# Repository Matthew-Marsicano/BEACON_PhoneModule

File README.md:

# BEACON Phone Module

KiCad 10 project for the BEACON phone module: a MagSafe-mounted board with an nRF52840, a 2.4 GHz receive chain
(patch antenna → BPF → LNA → nRF) and a CW transmit chain (LMX2582 synthesizer → CC2595 PA → U.FL to a Taoglas
FXP70 flex antenna). It is powered over USB-C.

**Ordering boards:** follow [`fab/JLCPCB_ORDER.md`](fab/JLCPCB_ORDER.md) (files to upload, board options, parts to check).
The wearable tag's JLCPCB package (exported from its Altium project) is in [`fab/wearable/`](fab/wearable/JLCPCB_ORDER.md).
To order both boards together, [`fab/panel/`](fab/panel/PANEL_ORDER.md) has a combined panel (one of each) with a merged BOM and CPL.

## Opening the project

Open `BEACON_PhoneModule.kicad_pro` in KiCad 10. The project's own libraries are referenced relative to the project
folder (`BEACON.kicad_sym`, `BEACON.pretty`, `BEACON_Routed.pretty`), so no library setup is needed.

| Path | Contents |
|---|---|
| `*.kicad_sch` | Root schematic + 6 sheets: USB, Power, MCU, RX_Frontend, TX_PA, CW_Synth |
| `BEACON_PhoneModule.kicad_pcb` | 4-layer board, 55 × 78.45 mm |
| `BEACON_PhoneModule.kicad_dru` | Custom design rules (JLCPCB limits, RF CPWG, USB pair, nRF aQFN escape) |
| `docs/` | Design notes, stackup and impedance, BOM (LCSC), reviews, hand-routing notes |
| `scripts/` | Python scripts used to generate and post-process the board (run with KiCad's Python) |
| `enclosure/` | OpenSCAD enclosure variants, STL and renders |
| `fab/` | JLCPCB outputs: Gerber/drill zip, BOM, CPL, PDFs, STEP, the one-zip package and the order sheet |
| `fab/wearable/` | Wearable tag JLCPCB outputs (Altium export): Gerber/drill zip, BOM, CPL, OutJob, order sheet |

## Board rules worth knowing

- **Stackup:** JLC04161H-7628, 1.6 mm. L1 signals and RF, **L2 solid GND (no tracks)**, L3 3V3 / VCC_SYN planes,
  L4 signals and USB pair.
- **No GND traces.** GND is copper fills on every layer plus vias; each GND pad has its own via to L2.
  3V3 and VCC_SYN pads have vias to their L3 areas. 5V0 and 5V_BUS are fills.
- **RF:** 50 Ω CPWG, 0.335 mm track, 0.203 mm gap, L1 only. RF and the USB D+/D− pair are locked; don't move them.
- **Vias:** 0.45/0.25 mm everywhere; 0.30/0.15 mm only as via-in-pad on the nRF (U5) balls. Order with
  JLC via-in-pad (POFV, filled and capped), ENIG and impedance control.
- Run DRC (Inspect → Design Rules Checker) before every commit. The remaining work is tracked in GitHub Issues.

## Working together

- **One person edits the PCB at a time.** `.kicad_pcb` is text, but two people's board edits don't merge cleanly.
  Say in the issue or team chat when you take the board, and push when you hand it back.
- Schematic sheets can be edited in parallel by different people (one sheet each).
- Save in KiCad, close the editor, then commit. Keep commits small and say what changed.

## Finishing steps (after routing is complete)

Run from this folder with KiCad's Python (`D:/KiCAD/bin/python.exe -I` on the original machine; adjust the path):

1. `scripts/stitch.py`: GND via fences along RF lines, perimeter and 3 mm grid stitching.
2. `kicad-cli pcb drc --format json -o drc.json BEACON_PhoneModule.kicad_pcb`, then `scripts/bridge_fills.py drc.json`
   to join any fill islands that are left unconnected.
3. `scripts/finish.py`: silkscreen clean-up and zone refill.
4. Final DRC with `--schematic-parity --refill-zones`, then `scripts/export_fab.py` (Gerbers, drill, BOM, CPL, STEP).

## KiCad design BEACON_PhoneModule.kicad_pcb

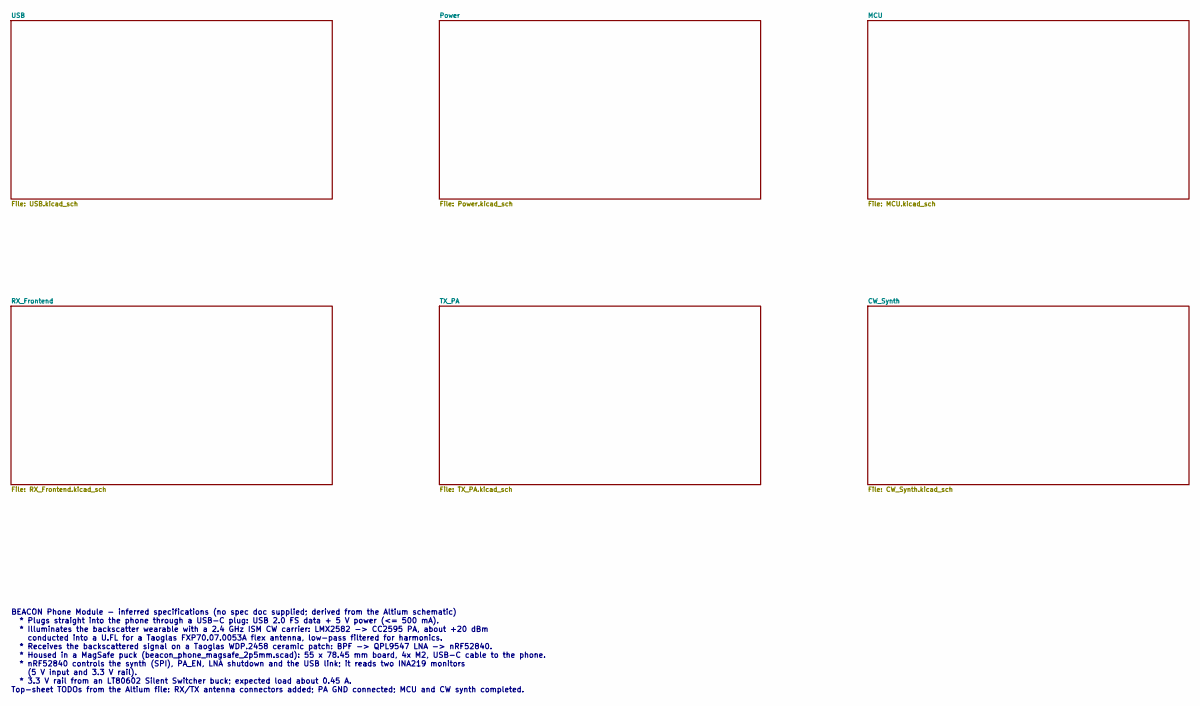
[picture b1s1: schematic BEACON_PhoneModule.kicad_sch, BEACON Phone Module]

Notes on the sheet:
BEACON Phone Module - inferred specifications (no spec doc supplied; derived from the Altium schematic) * Plugs straight into the phone through a USB-C plug: USB 2.0 FS data + 5 V power (<= 500 mA). * Illuminates the backscatter wearable with a 2.4 GHz ISM CW carrier: LMX2582 -> CC2595 PA, about +2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

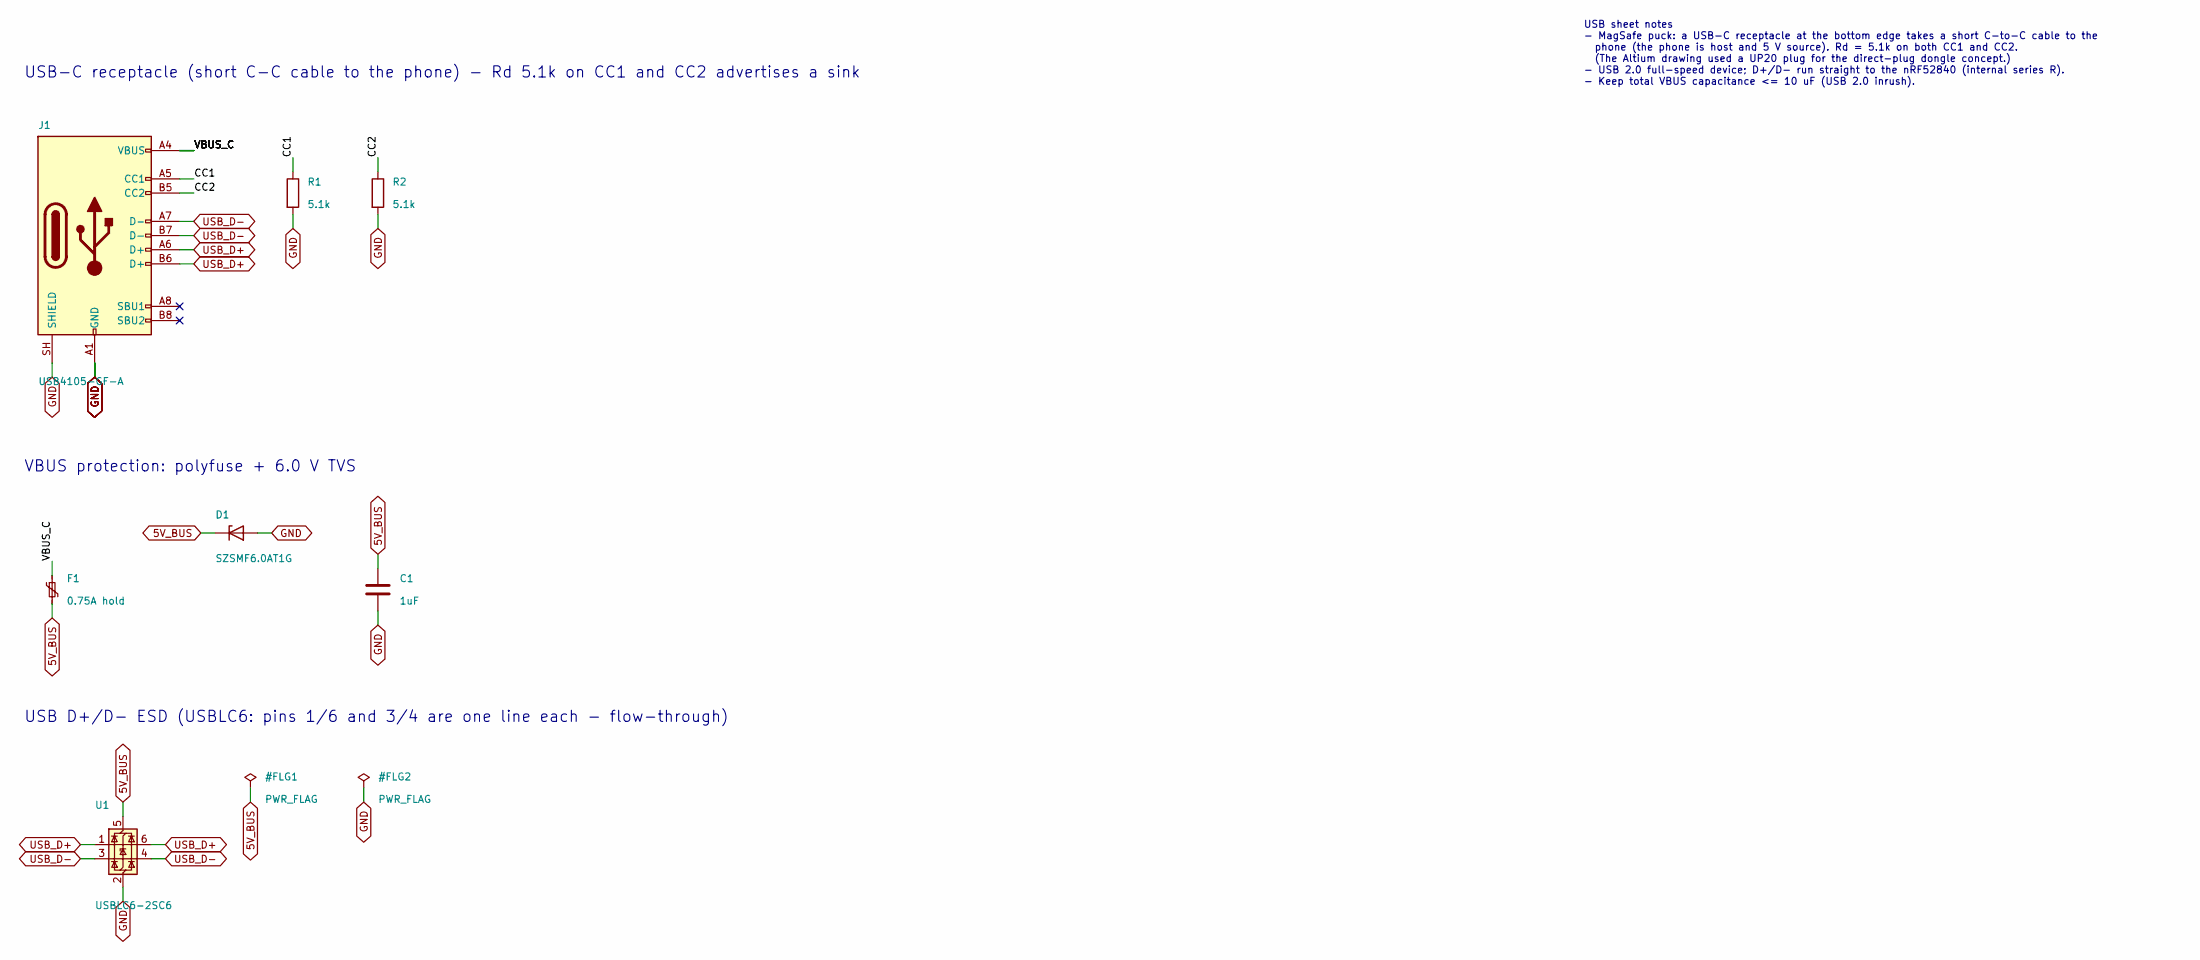
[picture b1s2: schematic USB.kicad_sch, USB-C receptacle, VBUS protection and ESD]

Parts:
C1: 1uF; C1_C_0402_1005Metric
D1: SZSMF6.0AT1G; D1_D_SOD-123F; MPN SZSMF6.0AT1G
F1: 0.75A hold; F1_Fuse_1206_3216Metric; MPN NANOSMDC075F-2
J1: USB4105-GF-A; J1_USB_C_Receptacle_GCT_USB4105-xx-A_16P_TopMnt_Horizontal; MPN USB4105-GF-A
R1: 5.1k; R1_R_0402_1005Metric
R2: 5.1k; R2_R_0402_1005Metric
U1: USBLC6-2SC6; U1_SOT-23-6; MPN USBLC6-2SC6

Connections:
5V_BUS: C1.1, D1.1 (K), F1.2, U1.5 (VBUS); also elsewhere on the board
/USB/CC1: J1.A5 (CC1), R1.1
/USB/CC2: J1.B5 (CC2), R2.1
/USB/VBUS_C: F1.1, J1.A4 (VBUS), J1.A9 (VBUS), J1.B4 (VBUS), J1.B9 (VBUS)
GND: C1.2, D1.2 (A), J1.A1 (GND), J1.A12 (GND), J1.B1 (GND), J1.B12 (GND), J1.SH (SHIELD), R1.2, R2.2, U1.2 (GND); also elsewhere on the board
USB_D+: J1.A6 (D+), J1.B6 (D+), U1.1 (I/O1), U1.6 (I/O1); also elsewhere on the board
USB_D-: J1.A7 (D-), J1.B7 (D-), U1.3 (I/O2), U1.4 (I/O2); also elsewhere on the board

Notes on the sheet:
USB-C receptacle (short C-C cable to the phone) - Rd 5.1k on CC1 and CC2 advertises a sink
VBUS protection: polyfuse + 6.0 V TVS
USB D+/D- ESD (USBLC6: pins 1/6 and 3/4 are one line each - flow-through)
USB sheet notes - MagSafe puck: a USB-C receptacle at the bottom edge takes a short C-to-C cable to the phone (the phone is host and 5 V source). Rd = 5.1k on both CC1 and CC2. (The Altium drawing used a UP20 plug for the direct-plug dongle concept.) - USB 2.0 full-speed device; D+/D- run straight 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

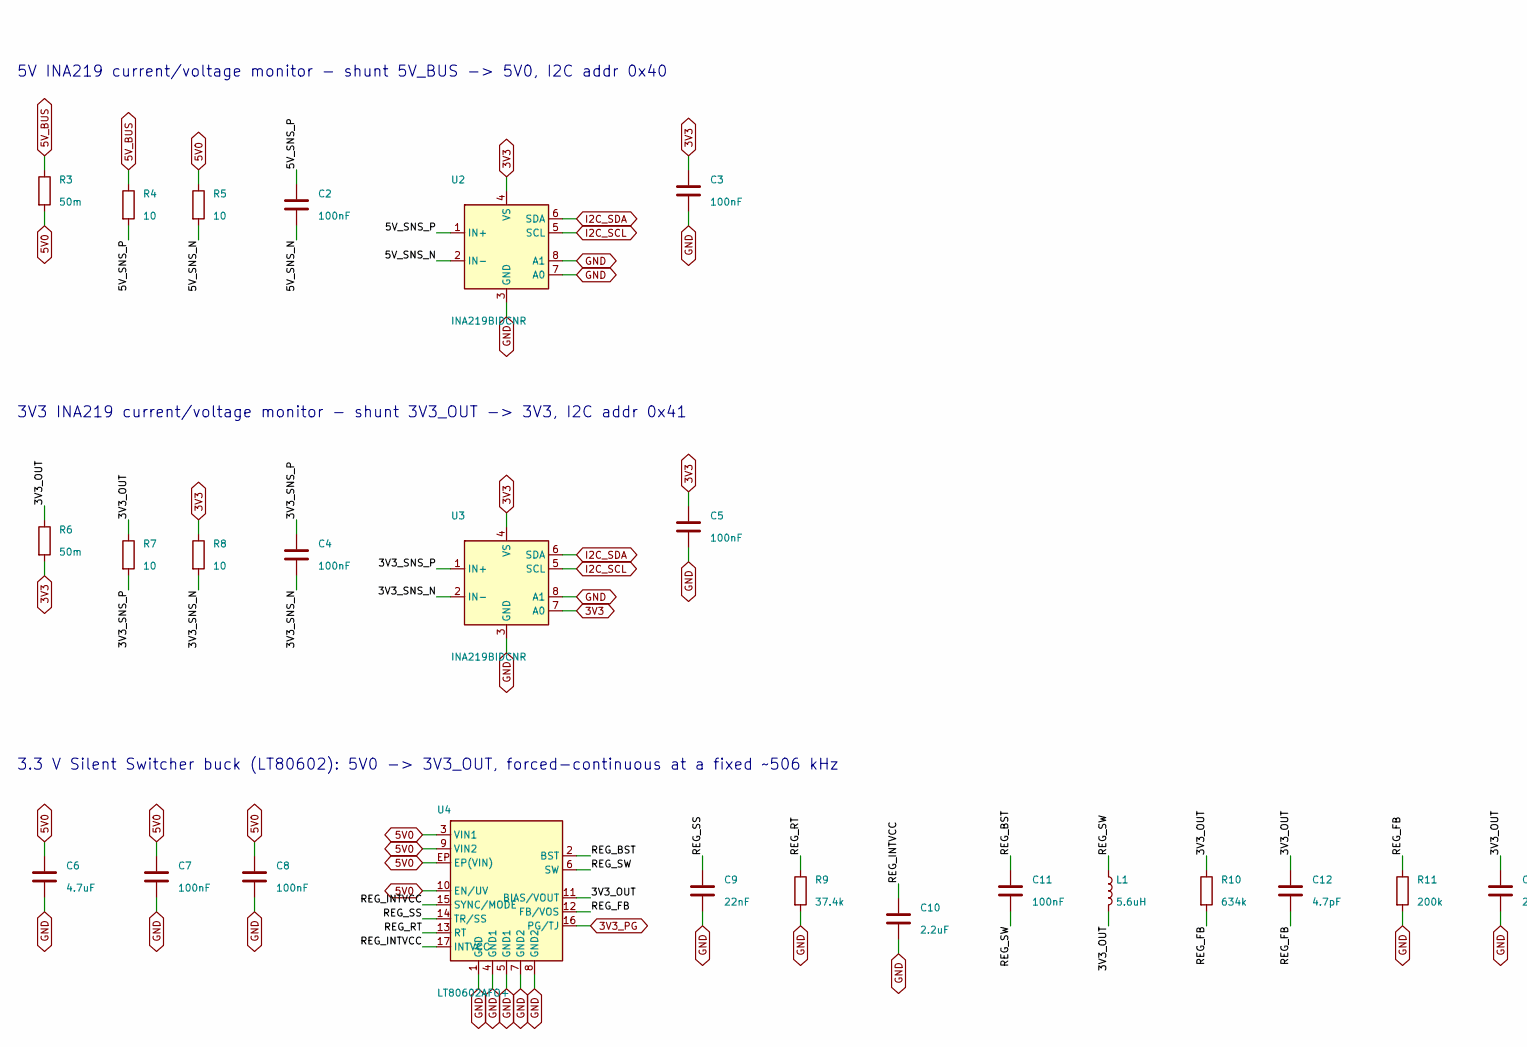
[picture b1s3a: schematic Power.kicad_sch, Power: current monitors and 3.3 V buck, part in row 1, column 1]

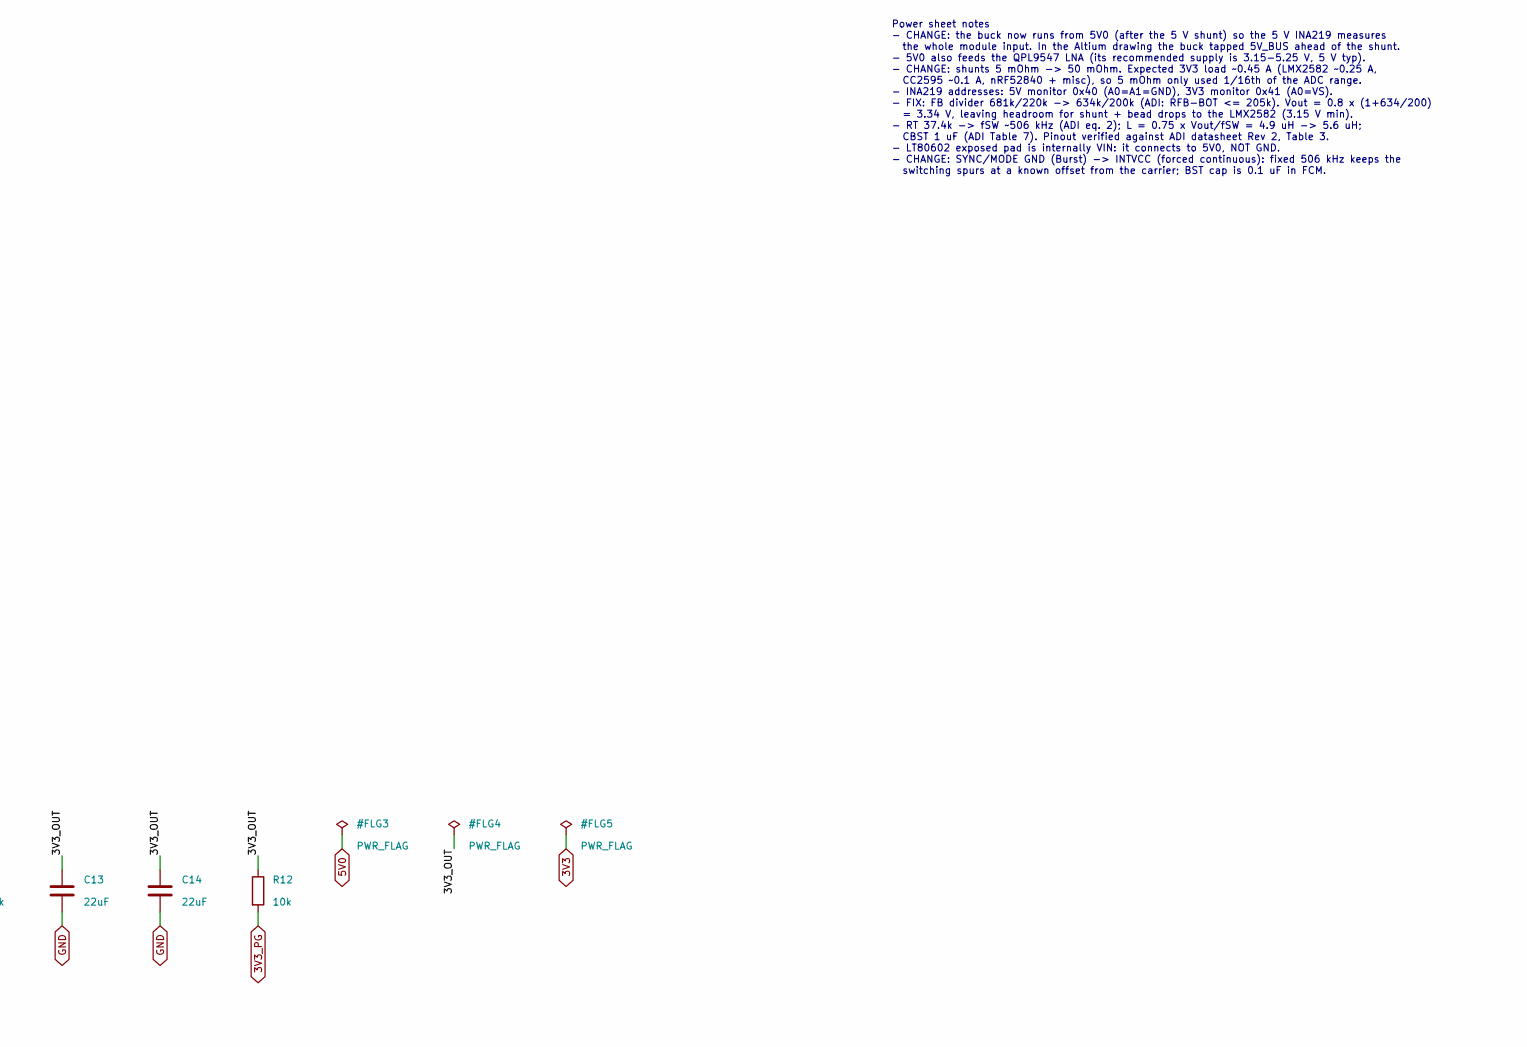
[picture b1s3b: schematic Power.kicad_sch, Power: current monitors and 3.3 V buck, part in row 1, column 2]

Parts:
C2: 100nF; C2_C_0402_1005Metric
C3: 100nF; C3_C_0402_1005Metric
C4: 100nF; C4_C_0402_1005Metric
C5: 100nF; C5_C_0402_1005Metric
C6: 4.7uF; C6_C_0603_1608Metric
C7: 100nF; C7_C_0402_1005Metric
C8: 100nF; C8_C_0402_1005Metric
C9: 22nF; C9_C_0402_1005Metric
C10: 2.2uF; C10_C_0603_1608Metric
C11: 100nF; C11_C_0402_1005Metric
C12: 4.7pF; C12_C_0402_1005Metric
C13: 22uF; C13_C_0805_2012Metric
C14: 22uF; C14_C_0805_2012Metric
L1: 5.6uH; L1_L_Abracon_ASPI-4030S; MPN ASPI-4030S-5R6M-T; LCSC C5224561
R3: 50m; R3_R_0805_2012Metric; Tolerance 1%; MPN ERJ-6BWFR050V
R4: 10; R4_R_0402_1005Metric
R5: 10; R5_R_0402_1005Metric
R6: 50m; R6_R_0805_2012Metric; Tolerance 1%; MPN ERJ-6BWFR050V
R7: 10; R7_R_0402_1005Metric
R8: 10; R8_R_0402_1005Metric
R9: 37.4k; R9_R_0402_1005Metric
R10: 634k; R10_R_0402_1005Metric
R11: 200k; R11_R_0402_1005Metric
R12: 10k; R12_R_0402_1005Metric
U2: INA219BIDCNR; U2_SOT-23-8; MPN INA219BIDCNR
U3: INA219BIDCNR; U3_SOT-23-8; MPN INA219BIDCNR
U4: LT80602AFO+; U4_ADI_FC2QFN-17-1EP_3x3mm_LT80602; MPN LT80602AFO+; LCSC C54448890

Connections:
3V3: C3.1, C5.1, R6.2, R8.1, U2.4 (VS), U3.4 (VS), U3.7 (A0); also elsewhere on the board
3V3_PG: R12.2, U4.16 (PG/TJ); also elsewhere on the board
5V0: C6.1, C7.1, C8.1, R3.2, R5.1, U4.3 (VIN1), U4.9 (VIN2), U4.10 (EN/UV), U4.EP (EP(VIN)); also elsewhere on the board
5V_BUS: R3.1, R4.1; also elsewhere on the board
/Power/3V3_OUT: C12.1, C13.1, C14.1, L1.2, R6.1, R7.1, R10.1, R12.1, U4.11 (BIAS/VOUT)
/Power/3V3_SNS_N: C4.2, R8.2, U3.2 (IN-)
/Power/3V3_SNS_P: C4.1, R7.2, U3.1 (IN+)
/Power/5V_SNS_N: C2.2, R5.2, U2.2 (IN-)
/Power/5V_SNS_P: C2.1, R4.2, U2.1 (IN+)
/Power/REG_BST: C11.1, U4.2 (BST)
/Power/REG_FB: C12.2, R10.2, R11.1, U4.12 (FB/VOS)
/Power/REG_INTVCC: C10.1, U4.15 (SYNC/MODE), U4.17 (INTVCC)
/Power/REG_RT: R9.1, U4.13 (RT)
/Power/REG_SS: C9.1, U4.14 (TR/SS)
/Power/REG_SW: C11.2, L1.1, U4.6 (SW)
GND: C3.2, C5.2, C6.2, C7.2, C8.2, C9.2, C10.2, C13.2, C14.2, R9.2, R11.2, U2.3 (GND), U2.7 (A0), U2.8 (A1), U3.3 (GND), U3.8 (A1), U4.1 (GND), U4.4 (GND1), U4.5 (GND1), U4.7 (GND2), U4.8 (GND2); also elsewhere on the board
I2C_SCL: U2.5 (SCL), U3.5 (SCL); also elsewhere on the board
I2C_SDA: U2.6 (SDA), U3.6 (SDA); also elsewhere on the board

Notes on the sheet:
5V INA219 current/voltage monitor - shunt 5V_BUS -> 5V0, I2C addr 0x40
3V3 INA219 current/voltage monitor - shunt 3V3_OUT -> 3V3, I2C addr 0x41
3.3 V Silent Switcher buck (LT80602): 5V0 -> 3V3_OUT, forced-continuous at a fixed ~506 kHz
Power sheet notes - CHANGE: the buck now runs from 5V0 (after the 5 V shunt) so the 5 V INA219 measures the whole module input. In the Altium drawing the buck tapped 5V_BUS ahead of the shunt. - 5V0 also feeds the QPL9547 LNA (its recommended supply is 3.15-5.25 V, 5 V typ). - CHANGE: shunts 5 mOhm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

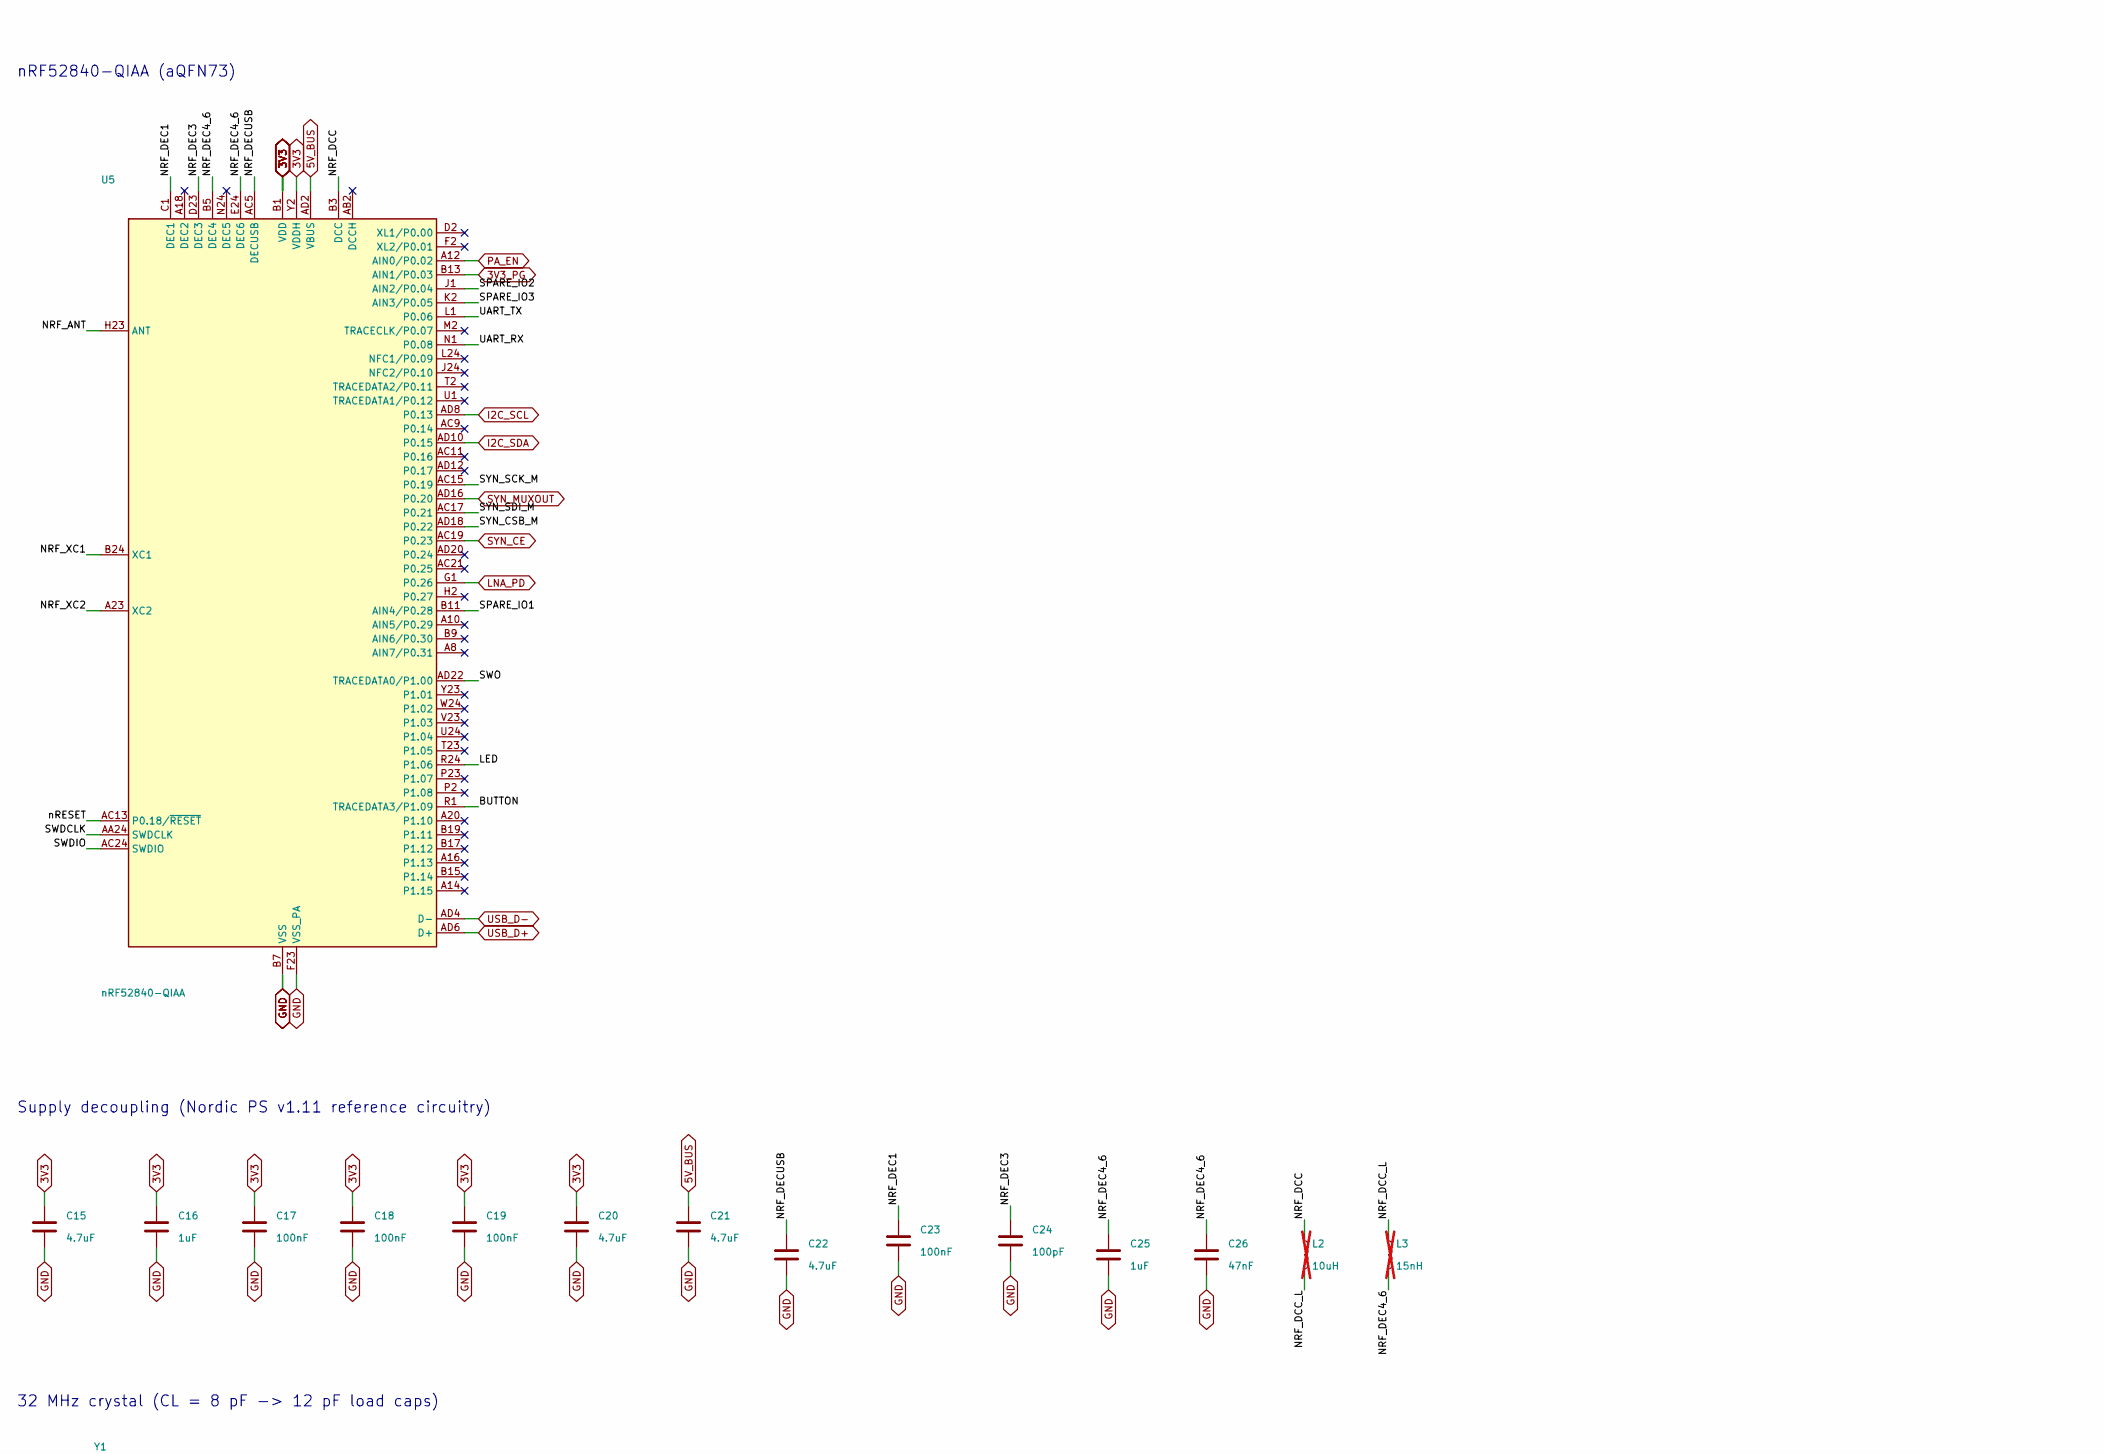
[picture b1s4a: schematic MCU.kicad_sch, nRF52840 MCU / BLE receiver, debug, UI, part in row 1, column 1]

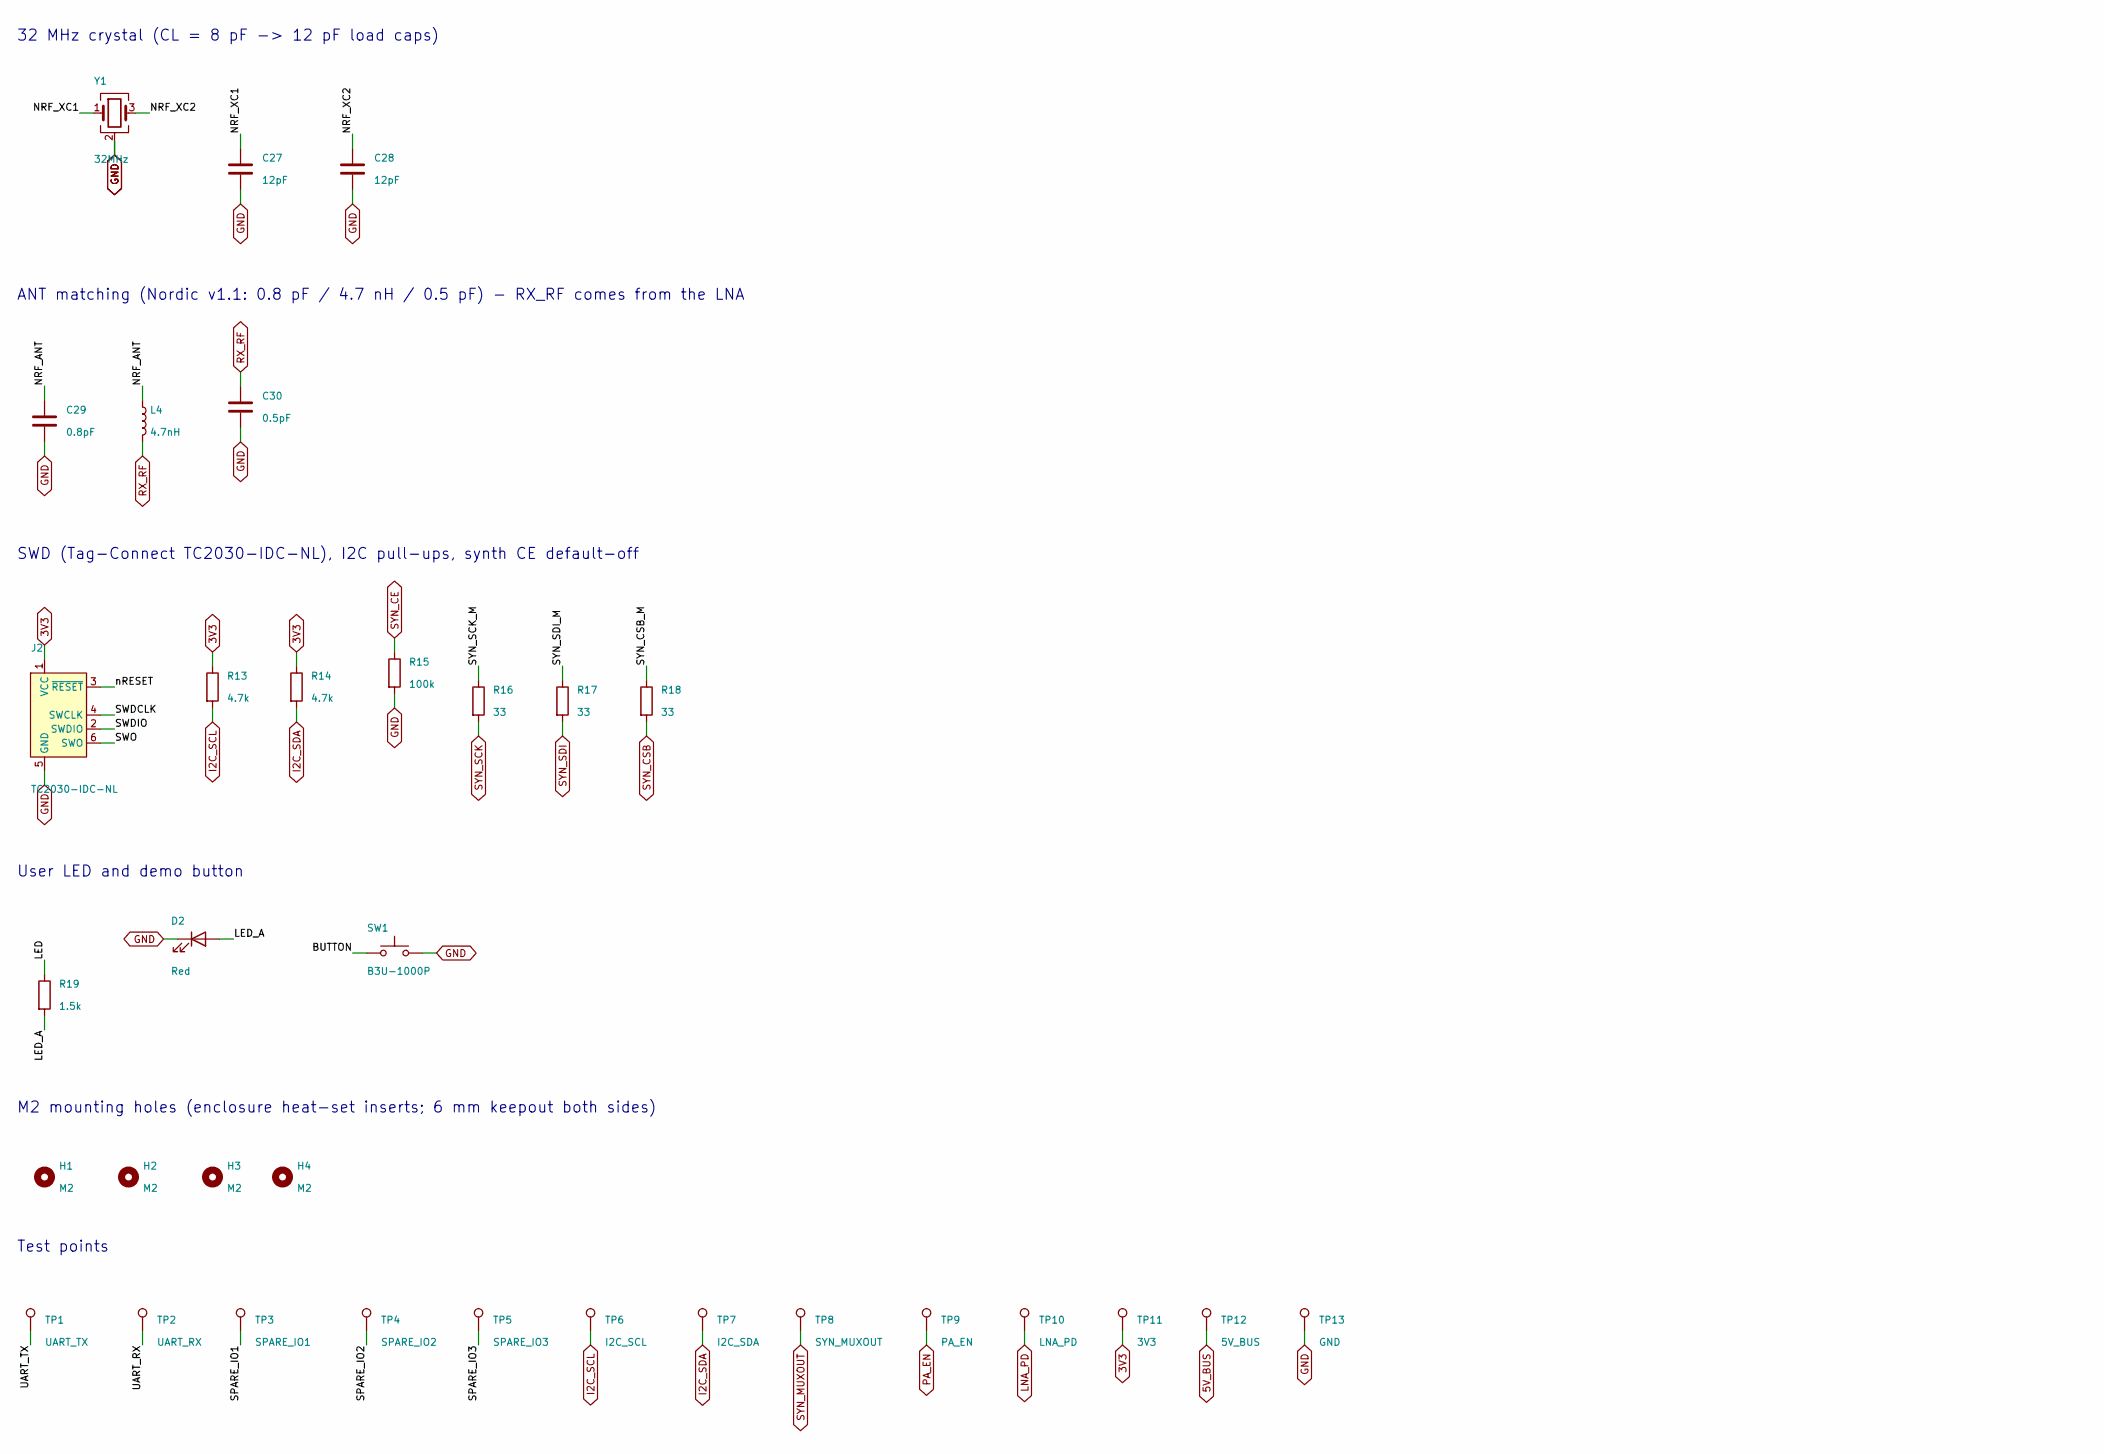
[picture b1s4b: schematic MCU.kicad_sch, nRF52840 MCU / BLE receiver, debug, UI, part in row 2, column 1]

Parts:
C15: 4.7uF; C15_C_0603_1608Metric
C16: 1uF; C16_C_0402_1005Metric
C17: 100nF; C17_C_0402_1005Metric
C18: 100nF; C18_C_0402_1005Metric
C19: 100nF; C19_C_0402_1005Metric
C20: 4.7uF; C20_C_0603_1608Metric
C21: 4.7uF; C21_C_0603_1608Metric
C22: 4.7uF; C22_C_0603_1608Metric
C23: 100nF; C23_C_0402_1005Metric
C24: 100pF; C24_C_0402_1005Metric
C25: 1uF; C25_C_0402_1005Metric
C26: 47nF; C26_C_0402_1005Metric
C27: 12pF; C27_C_0402_1005Metric
C28: 12pF; C28_C_0402_1005Metric
C29: 0.8pF; C29_C_0402_1005Metric; MPN GJM1555C1HR80BB01D
C30: 0.5pF; C30_C_0402_1005Metric; MPN GJM1555C1HR50BB01D
D2: Red; D2_LED_0603_1608Metric; MPN KT-0603R
H1: M2; H1_MountingHole_2.2mm_M2
H2: M2; H2_MountingHole_2.2mm_M2
H3: M2; H3_MountingHole_2.2mm_M2
H4: M2; H4_MountingHole_2.2mm_M2
J2: TC2030-IDC-NL; J2_Tag-Connect_TC2030-IDC-NL_2x03_P1.27mm_Vertical
L2: 10uH; L2_L_0603_1608Metric; MPN LQM18PN100MFRL; not fitted
L3: 15nH; L3_L_0402_1005Metric; MPN LQG15HS15NJ02D; not fitted
L4: 4.7nH; L4_L_0402_1005Metric; MPN LQG15HS4N7B02D; LCSC C162543
R13: 4.7k; R13_R_0402_1005Metric
R14: 4.7k; R14_R_0402_1005Metric
R15: 100k; R15_R_0402_1005Metric
R16: 33; R16_R_0402_1005Metric
R17: 33; R17_R_0402_1005Metric
R18: 33; R18_R_0402_1005Metric
R19: 1.5k; R19_R_0402_1005Metric
SW1: B3U-1000P; SW1_SW_SPST_B3U-1000P; MPN B3U-1000P
TP1: UART_TX; TP1_TestPoint_Pad_D1.0mm
TP2: UART_RX; TP2_TestPoint_Pad_D1.0mm
TP3: SPARE_IO1; TP3_TestPoint_Pad_D1.0mm
TP4: SPARE_IO2; TP4_TestPoint_Pad_D1.0mm
TP5: SPARE_IO3; TP5_TestPoint_Pad_D1.0mm
TP6: I2C_SCL; TP6_TestPoint_Pad_D1.0mm
TP7: I2C_SDA; TP7_TestPoint_Pad_D1.0mm
TP8: SYN_MUXOUT; TP8_TestPoint_Pad_D1.0mm
TP9: PA_EN; TP9_TestPoint_Pad_D1.0mm
TP10: LNA_PD; TP10_TestPoint_Pad_D1.0mm
TP11: 3V3; TP11_TestPoint_Pad_D1.0mm
TP12: 5V_BUS; TP12_TestPoint_Pad_D1.0mm
TP13: GND; TP13_TestPoint_Pad_D1.0mm
U5: nRF52840-QIAA; U5_Nordic_AQFN-73-1EP_7x7mm_P0.5mm; MPN NRF52840-QIAA-R
Y1: 32MHz; Y1_Crystal_SMD_2016-4Pin_2.0x1.6mm; MPN ABM11W-32.0000MHZ-8-B1U-T3

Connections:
3V3: C15.1, C16.1, C17.1, C18.1, C19.1, C20.1, J2.1 (VCC), R13.1, R14.1, TP11.1, U5.A22 (VDD), U5.AD14 (VDD), U5.AD23 (VDD), U5.B1 (VDD), U5.W1 (VDD), U5.Y2 (VDDH); also elsewhere on the board
3V3_PG: U5.B13 (AIN1/P0.03); also elsewhere on the board
5V_BUS: C21.1, TP12.1, U5.AD2 (VBUS); also elsewhere on the board
/MCU/BUTTON: SW1.1, U5.R1 (TRACEDATA3/P1.09)
/MCU/LED: R19.1, U5.R24 (P1.06)
/MCU/LED_A: D2.2 (A), R19.2
/MCU/NRF_ANT: C29.1, L4.1, U5.H23 (ANT)
/MCU/NRF_DCC: L2.1, U5.B3 (DCC)
/MCU/NRF_DCC_L: L2.2, L3.1
/MCU/NRF_DEC1: C23.1, U5.C1 (DEC1)
/MCU/NRF_DEC3: C24.1, U5.D23 (DEC3)
/MCU/NRF_DEC4_6: C25.1, C26.1, L3.2, U5.B5 (DEC4), U5.E24 (DEC6)
/MCU/NRF_DECUSB: C22.1, U5.AC5 (DECUSB)
/MCU/NRF_XC1: C27.1, U5.B24 (XC1), Y1.1
/MCU/NRF_XC2: C28.1, U5.A23 (XC2), Y1.3
/MCU/SPARE_IO1: TP3.1, U5.B11 (AIN4/P0.28)
/MCU/SPARE_IO2: TP4.1, U5.J1 (AIN2/P0.04)
/MCU/SPARE_IO3: TP5.1, U5.K2 (AIN3/P0.05)
/MCU/SWDCLK: J2.4 (SWCLK), U5.AA24 (SWDCLK)
/MCU/SWDIO: J2.2 (SWDIO), U5.AC24 (SWDIO)
/MCU/SWO: J2.6 (SWO), U5.AD22 (TRACEDATA0/P1.00)
/MCU/SYN_CSB_M: R18.1, U5.AD18 (P0.22)
/MCU/SYN_SCK_M: R16.1, U5.AC15 (P0.19)
/MCU/SYN_SDI_M: R17.1, U5.AC17 (P0.21)
/MCU/UART_RX: TP2.1, U5.N1 (P0.08)
/MCU/UART_TX: TP1.1, U5.L1 (P0.06)
/MCU/nRESET: J2.3 (~RESET), U5.AC13 (P0.18/~RESET)
GND: C15.2, C16.2, C17.2, C18.2, C19.2, C20.2, C21.2, C22.2, C23.2, C24.2, C25.2, C26.2, C27.2, C28.2, C29.2, C30.2, D2.1 (K), J2.5 (GND), R15.2, SW1.2, TP13.1, U5.B7 (VSS), U5.EP (VSS), U5.F23 (VSS_PA), Y1.2 (G), Y1.4 (G); also elsewhere on the board
I2C_SCL: R13.2, TP6.1, U5.AD8 (P0.13); also elsewhere on the board
I2C_SDA: R14.2, TP7.1, U5.AD10 (P0.15); also elsewhere on the board
LNA_PD: TP10.1, U5.G1 (P0.26); also elsewhere on the board
PA_EN: TP9.1, U5.A12 (AIN0/P0.02); also elsewhere on the board
RX_RF: C30.1, L4.2; also elsewhere on the board
SYN_CE: R15.1, U5.AC19 (P0.23); also elsewhere on the board
SYN_CSB: R18.2; also elsewhere on the board
SYN_MUXOUT: TP8.1, U5.AD16 (P0.20); also elsewhere on the board
SYN_SCK: R16.2; also elsewhere on the board
SYN_SDI: R17.2; also elsewhere on the board
USB_D+: U5.AD6 (D+); also elsewhere on the board
USB_D-: U5.AD4 (D-); also elsewhere on the board

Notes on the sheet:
nRF52840-QIAA (aQFN73)
Supply decoupling (Nordic PS v1.11 reference circuitry)
32 MHz crystal (CL = 8 pF -> 12 pF load caps)
ANT matching (Nordic v1.1: 0.8 pF / 4.7 nH / 0.5 pF) - RX_RF comes from the LNA
SWD (Tag-Connect TC2030-IDC-NL), I2C pull-ups, synth CE default-off
User LED and demo button
M2 mounting holes (enclosure heat-set inserts; 6 mm keepout both sides)
Test points
MCU sheet notes - Supply: VDD and VDDH both on 3V3 (normal-voltage mode); DCCH unused. REG1 runs in LDO mode (firmware DCDCEN=0): the 10 uH ferrite would saturate in the MagSafe magnet field, so the DC/DC inductors are DNP footprints. VBUS from USB for the USBD peripheral. - Removed wearable-only n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

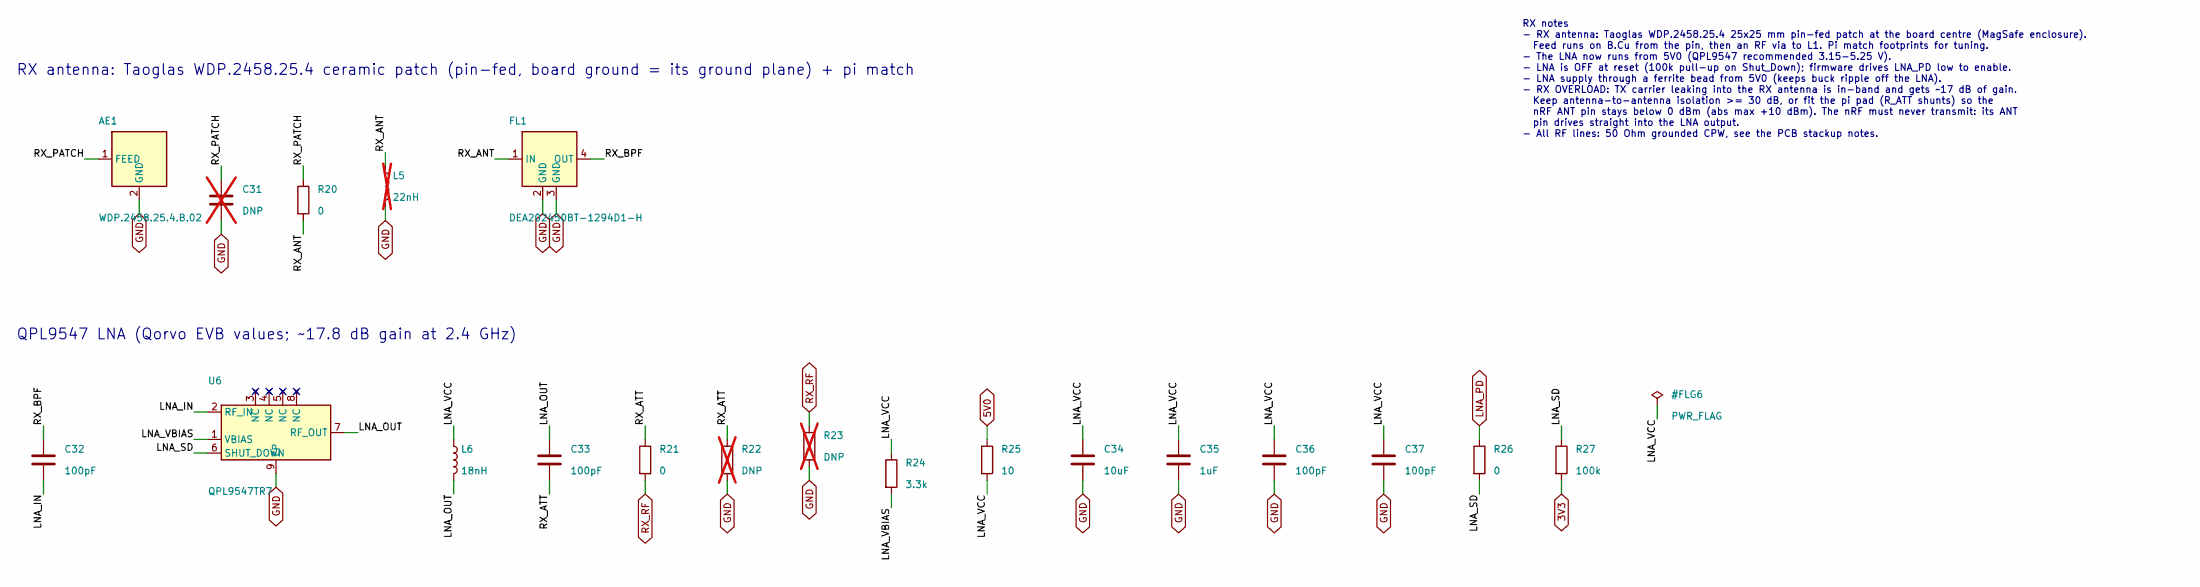
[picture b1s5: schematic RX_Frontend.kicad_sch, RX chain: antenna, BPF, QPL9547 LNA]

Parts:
AE1: WDP.2458.25.4.B.02; AE1_Taoglas_WDP.2458.25.4_Patch; MPN WDP.2458.25.4.B.02
C31: DNP; C31_C_0402_1005Metric; not fitted
C32: 100pF; C32_C_0402_1005Metric
C33: 100pF; C33_C_0402_1005Metric
C34: 10uF; C34_C_0603_1608Metric
C35: 1uF; C35_C_0402_1005Metric
C36: 100pF; C36_C_0402_1005Metric
C37: 100pF; C37_C_0402_1005Metric
FL1: DEA202450BT-1294D1-H; FL1_TDK_DEA202450BT-1294D1-H_2012; MPN DEA202450BT-1294D1-H; LCSC C1512913
L5: 22nH; L5_L_0402_1005Metric; MPN LQW15AN22NJ00D; not fitted
L6: 18nH; L6_L_0402_1005Metric; MPN 0402CS-18NXGRW
R20: 0; R20_R_0402_1005Metric
R21: 0; R21_R_0402_1005Metric
R22: DNP; R22_R_0402_1005Metric; not fitted
R23: DNP; R23_R_0402_1005Metric; not fitted
R24: 3.3k; R24_R_0402_1005Metric
R25: 10; R25_R_0603_1608Metric
R26: 0; R26_R_0402_1005Metric
R27: 100k; R27_R_0402_1005Metric
U6: QPL9547TR7; U6_Qorvo_QPL9547_DFN-8-1EP_2x2mm_P0.5mm; MPN QPL9547TR7

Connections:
3V3: R27.2; also elsewhere on the board
5V0: R25.1; also elsewhere on the board
/RX_Frontend/LNA_IN: C32.2, U6.2 (RF_IN)
/RX_Frontend/LNA_OUT: C33.1, L6.2, U6.7 (RF_OUT)
/RX_Frontend/LNA_SD: R26.2, R27.1, U6.6 (SHUT_DOWN)
/RX_Frontend/LNA_VBIAS: R24.2, U6.1 (VBIAS)
/RX_Frontend/LNA_VCC: C34.1, C35.1, C36.1, C37.1, L6.1, R24.1, R25.2
/RX_Frontend/RX_ANT: FL1.1 (IN), L5.1, R20.2
/RX_Frontend/RX_ATT: C33.2, R21.1, R22.1
/RX_Frontend/RX_BPF: C32.1, FL1.4 (OUT)
/RX_Frontend/RX_PATCH: AE1.1 (FEED), C31.1, R20.1
GND: AE1.2 (GND), C31.2, C34.2, C35.2, C36.2, C37.2, FL1.2 (GND), FL1.3 (GND), L5.2, R22.2, R23.2, U6.9 (EP); also elsewhere on the board
LNA_PD: R26.1; also elsewhere on the board
RX_RF: R21.2, R23.1; also elsewhere on the board

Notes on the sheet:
RX antenna: Taoglas WDP.2458.25.4 ceramic patch (pin-fed, board ground = its ground plane) + pi match
QPL9547 LNA (Qorvo EVB values; ~17.8 dB gain at 2.4 GHz)
RX notes - RX antenna: Taoglas WDP.2458.25.4 25x25 mm pin-fed patch at the board centre (MagSafe enclosure). Feed runs on B.Cu from the pin, then an RF via to L1. Pi match footprints for tuning. - The LNA now runs from 5V0 (QPL9547 recommended 3.15-5.25 V). - LNA is OFF at reset (100k pull-up on Sh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
